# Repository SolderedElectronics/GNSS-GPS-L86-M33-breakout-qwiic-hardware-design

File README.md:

# GNSS GPS L86-M33 breakout qwiic Hardware Design

## About the Product

|  |
| :----------------------------------------------------------: |
| [Buy GNSS GPS L86-M33 breakout qwiic](https://www.solde.red/333213) |

Global Navigation Satellite Signal Systems (GNSS), or as we all like to call it “GPS”, enable precise location determination on Earth. Thanks to this module, you can use GNSS for your project and use the device for asset tracking or create a wearable device. The module is small, energy-efficient, high-performing, and easy to use thanks to the built-in antenna.

L86-M33 is a GNSS receiver, which means it can receive signals from GPS, GLONASS, and Galileo constellations. Equipped with EASY (Embedded Assist System for self-generated orbit prediction) and AlwaysLocate technologies, L86-M33 ensures fast and accurate positioning even in challenging environments. Its advanced internal logger LOCUS allows you to store your routes and location data.

Our breakout board, in addition to the previously mentioned L86-M33 module which has an integrated antenna, also has a connector for a CR1220 battery which is used as a backup for timekeeping and GPS data. The module can operate without the battery, but every time it will have to fetch data from satellites afresh (cold start). If the integrated antenna is insufficient, there is an IPX connector on the board for adding an external, stronger antenna. To easily access the module pins, the pins are extended on the board for accessibility. There is also a switch on the board to change the I2C address.

---

## Repository Contents

This repository contains all design files for GNSS GPS L86-M33 breakout qwiic, organized as follows:

- **`CAD` folder**: Contains KiCAD design files, including:
  - Schematics
  - PCB layout
  - Panel PCB layout
  - Source 3D files in Fusion360, if any
  - All files are sorted by version with a detailed change log.
- **`OUTPUTS` folder**: Includes all production-ready files, such as:
  - Bill of Materials (BOM) and interactive BOM (iBOM)
  - PDF versions of schematics
  - 3D `.step` file of the board
  - 3D-printable models
  - Gerber files for PCB manufacturing
  - Image of the pinout of the board
  - Product image
  - Compliance, legal and generic sales documents

Refer to the `Change Log` in the CAD folder for details about updates between versions.

---

## Learn More About the Product

Beyond the repository, explore the following resources:

### Soldered Verify

The **Soldered Verify** system ensures every board you purchase from Soldered is fully functional. It also provides access to exclusive test data for your product. To get started, find the unique Soldered Verify ID on your product's packaging and enter the ID on the [Soldered Verify page](https://soldered.com/verify/) to access test results and additional product details.

### Soldered Community

Soldered Community is your go-to place for technical support. Our engineers track and answer all questions posted there, and it’s a great space for the maker community. Get answers to your questions and solutions for your challenges at [Soldered Community](https://soldered.com/community).

### solde.red

solde.red is an ultimate URL shortener and information hub. Access it by typing solde.red/ followed by your product SKU, e.g., [solde.red/333000](https://solde.red/333000), to find getting-started guides, datasheets, open-source hardware and software files, certifications, images, pinouts, and more. Read more about the shortener [here](https://solde.red/info/).

---

## Contributing

Contributions are welcome! Here’s how you can get involved:

- Submit pull requests to enhance the design or fix issues.
- Report bugs or problems by opening an issue.

We encourage community collaboration to make this product even better.

---

## About Soldered

[Soldered for Makers](https://soldered.com) specializes in designing and manufacturing electronic products tailored for enthusiasts, ranging from hobbyists to professionals. Our portfolio includes electronic boards, sensors, and actuators that are widely utilized in fields such as microelectronics, mechatronics, robotics, programming, and IoT. Every product we offer is designed in-house and built upon open-source hardware and software platforms. Proudly certified and manufactured within the European Union, our catalog likely includes the product you need for your project.

We complement these products with comprehensive tutorials and manuals, product descriptions, schematics, programming codes, and project examples. Our round-the-clock [customer and technical support](https://soldered.com/community) is available for all our products, irrespective of the sales channel. Soldered’s success and services reflect our maker community’s unwavering [trust](https://www.trustpilot.com/review/soldered.com), for which we are deeply grateful. Join our community and create using Soldered products.

---

## License

All Soldered open-source hardware (OSH) is under The TAPR Open Hardware License. Read more in the LICENSE file located in this repository.

**Disclaimer:**

No warranty - all designs in this repository are distributed in the hope that they will be useful, but without any warranty. They are provided "AS IS", therefore without warranty of any kind, either expressed or implied. The entire quality and performance of what you do with the contents of this repository are your responsibility. In no event Soldered Electronics will be liable for your damages, or losses, including any general, special, incidental, or consequential damage arising out of the use or inability to use the contents of this repository. 

---

## Have fun!

Thank you for your support from your fellow makers at Soldered Electronics.

Happy Making!

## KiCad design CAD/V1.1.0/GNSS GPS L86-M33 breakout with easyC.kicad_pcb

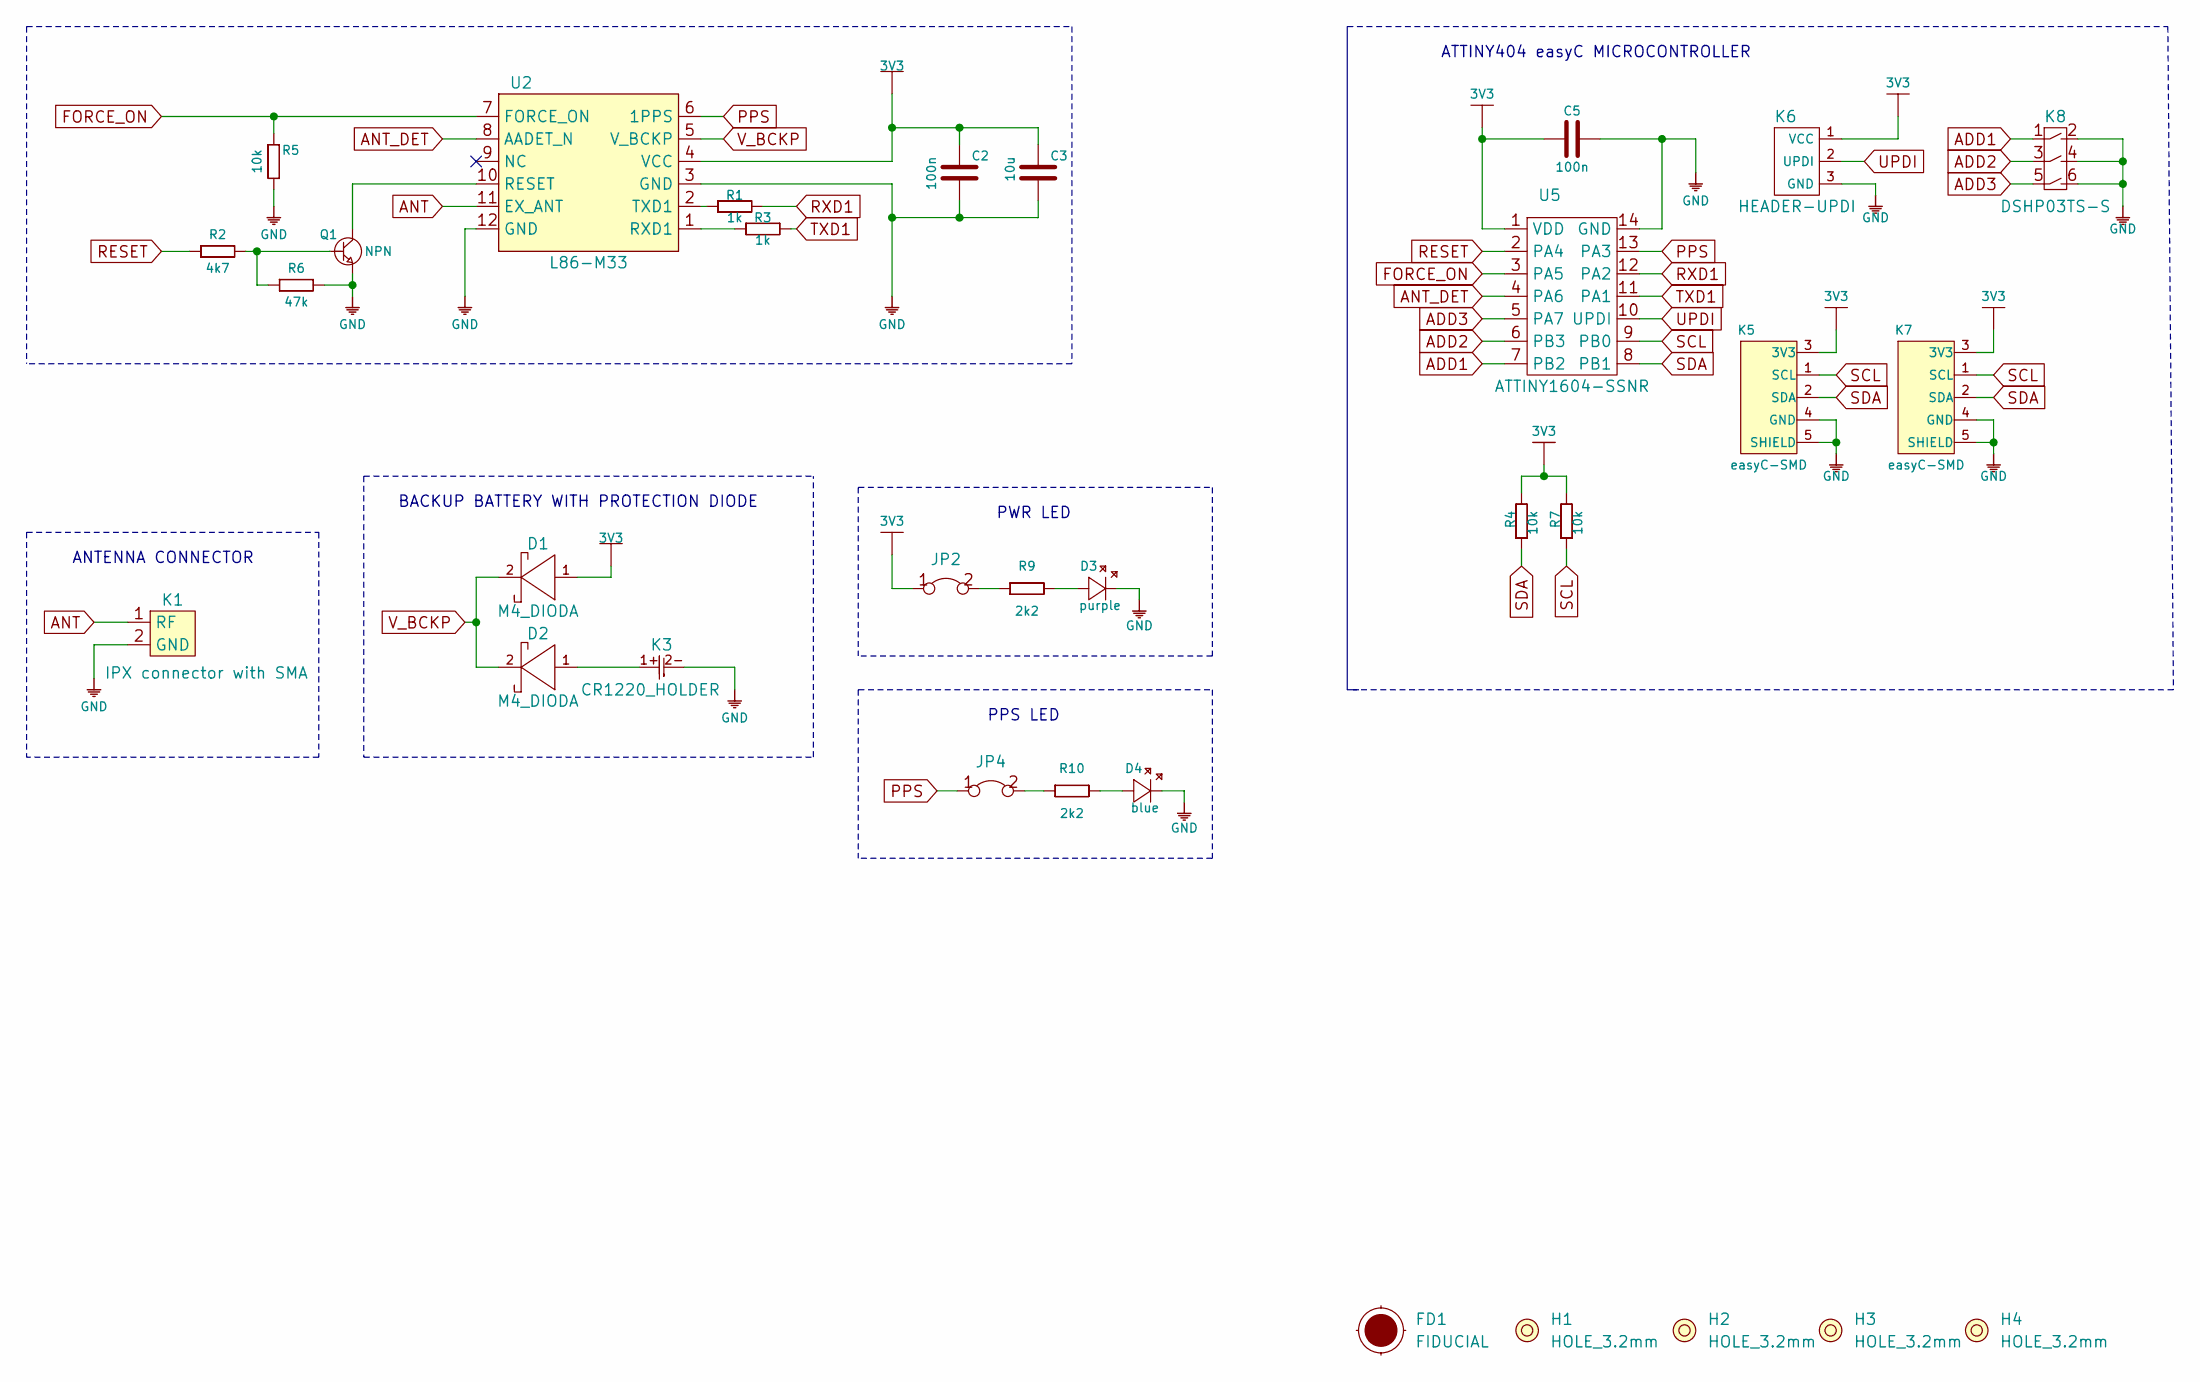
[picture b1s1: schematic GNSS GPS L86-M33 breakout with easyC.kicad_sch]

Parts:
C2, C5: 100n; 0603C
C3: 10u; 1206C
D1, D2: M4_DIODA
D3: purple; 0402LED
D4: blue; 0402LED
FD1: FIDUCIAL; FIDUCIAL_23
H1, H2, H3, H4: HOLE_3.2mm
JP2, JP4: SMD-JUMPER-CONNECTED_TRACE_SOLDERMASK
K1: IPX connector with SMA
K3: CR1220_HOLDER
K5, K7: easyC-SMD; easyC-connector
K6: HEADER-UPDI
K8: DSHP03TS-S
Q1: NPN; SOT-23-3
R1, R3: 1k; 0603R
R2: 4k7; 0603R
R4, R5, R7: 10k; 0603R
R6: 47k; 0603R
R9, R10: 2k2; 0402R
U2: L86-M33
U5: ATTINY1604-SSNR; SOIC-14

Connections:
3V3: C2.2, C3.2, C5.1, D1.1 (A), JP2.1, K5.3 (3V3), K6.1 (VCC), K7.3 (3V3), R4.2, R7.2, U2.4 (VCC), U5.1 (VDD)
ADD1: K8.1, U5.7 (PB2)
ADD2: K8.3, U5.6 (PB3)
ADD3: K8.5, U5.5 (PA7)
ANT: K1.1 (RF), U2.11 (EX_ANT)
ANT_DET: U2.8 (AADET_N), U5.4 (PA6)
FORCE_ON: R5.1, U2.7 (FORCE_ON), U5.3 (PA5)
GND: C2.1, C3.1, C5.2, D3.2 (K), D4.2 (K), K1.2 (GND), K3.2-, K5.4 (GND), K5.5 (SHIELD), K6.3 (GND), K7.4 (GND), K7.5 (SHIELD), K8.2, K8.4, K8.6, Q1.2 (E), R5.2, R6.2, U2.3 (GND), U2.12 (GND), U5.14 (GND)
unnamed: D2.1 (A), K3.1+
unnamed: D3.1 (A), R9.2
unnamed: D4.1 (A), R10.2
unnamed: JP2.2, R9.1
unnamed: JP4.2, R10.1
unnamed: Q1.1 (B), R2.2, R6.1
unnamed: Q1.3 (C), U2.10 (RESET)
unnamed: R1.1, U2.2 (TXD1)
unnamed: R3.1, U2.1 (RXD1)
PPS: JP4.1, U2.6 (1PPS), U5.13 (PA3)
RESET: R2.1, U5.2 (PA4)
RXD1: R1.2, U5.12 (PA2)
SCL: K5.1 (SCL), K7.1 (SCL), R7.1, U5.9 (PB0)
SDA: K5.2 (SDA), K7.2 (SDA), R4.1, U5.8 (PB1)
TXD1: R3.2, U5.11 (PA1)
UPDI: K6.2 (UPDI), U5.10 (UPDI)
V_BCKP: D1.2 (K), D2.2 (K), U2.5 (V_BCKP)

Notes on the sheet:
PPS LED
BACKUP BATTERY WITH PROTECTION DIODE
ATTINY404 easyC MICROCONTROLLER
ANTENNA CONNECTOR
PWR LED

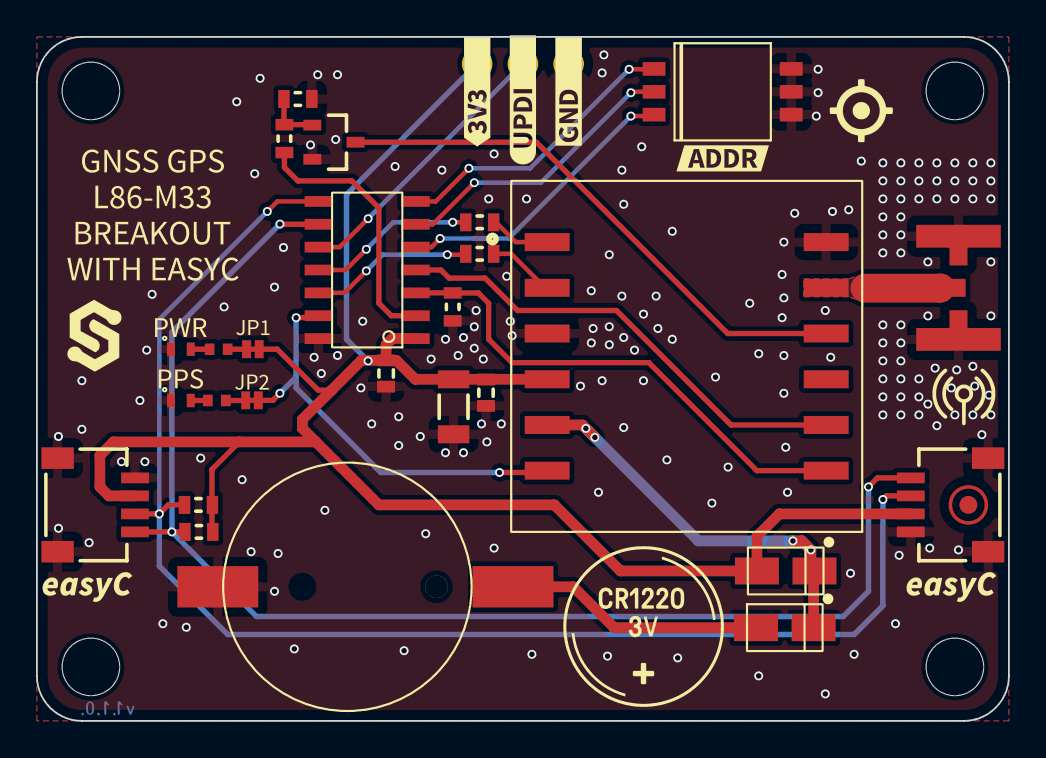
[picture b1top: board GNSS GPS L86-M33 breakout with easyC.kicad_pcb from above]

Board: 2 copper layers, 54.0 x 38.0 mm, 45 parts (1 on the bottom side), 25 nets.

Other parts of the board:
Ref**: Val**; Version1.1.0
kibuzzard-646B10BE: G***; kibuzzard-646B10BE
kibuzzard-646B10CD: G***; kibuzzard-646B10CD
kibuzzard-646B10D8: G***; kibuzzard-646B10D8
kibuzzard-646B10E4: G***; kibuzzard-646B10E4
kibuzzard-646B110E: G***; kibuzzard-646B110E
kibuzzard-646B122B: G***; kibuzzard-646B122B
kibuzzard-646B123E: G***; kibuzzard-646B123E
kibuzzard-646B1119: G***; kibuzzard-646B1119
kibuzzard-646B1126: G***; kibuzzard-646B1126
kibuzzard-646B1134: G***; kibuzzard-646B1134
kibuzzard-646B1202: G***; kibuzzard-646B1202
kibuzzard-646B1217: G***; kibuzzard-646B1217

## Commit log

2025-01-28 Updating open source files.
